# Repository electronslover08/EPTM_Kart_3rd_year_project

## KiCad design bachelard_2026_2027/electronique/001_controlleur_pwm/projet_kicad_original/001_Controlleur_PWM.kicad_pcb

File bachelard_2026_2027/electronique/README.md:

# ⚡ Électronique

Ce dossier contient les **schémas électroniques et les fichiers KiCad** du kart (KiCad 10) :

- **PCB de commande à distance** : lecture du récepteur radio, commande de l'accélération, du frein et de la direction, sélection du mode (manuel / à distance) ;
- **sécurités** : détection de la perte de liaison, arrêt d'urgence, chien de garde indépendant du microcontrôleur ;
- monitoring au volant et câblage.

Licence : [CERN-OHL-P-2.0](../../.github/LICENSES/CERN-OHL-P-2.0.txt). En cas de modification, indique la **date** et une **brève description** du changement (exigence de la licence).

## Contenu (état au 27.11.2026)

| Dossier | Contenu |
|---|---|
| [`001_controlleur_pwm/`](001_controlleur_pwm/) | Contrôleur PWM : lecture des 6 voies du récepteur, sortie RS-485. `projet_kicad_original/` = fichiers d'origine (ne pas modifier) ; `projet_kicad_version_eptm/` = version de travail pour la gravure EPTM (règles `.kicad_dru`, points de test dans `points_de_test.md`) |
| [`002_controleur_moteur/`](002_controleur_moteur/) | Contrôleur moteur : projet KICAD commencé (schéma, PCB vide) |
| [`xxx_modele_pcb/`](xxx_modele_pcb/) | Projet KiCad modèle, à copier pour un nouveau PCB |
| [`prompt_reprise_points_de_test_271126.md`](prompt_reprise_points_de_test_271126.md) | Note de reprise du PCB 001 : état, règles EPTM, points de test TP1 à TP7 |

## Bibliothèques tierces

Le symbole `lib_PIC18F45K22/PIC18F45K22-I_PT.kicad_sym` et l'empreinte TQFP-44 viennent de **SnapEDA / SnapMagic** (pièce Microchip PIC18F45K22-I/PT, récupérés le 26.11.2026). Ils ne sont **pas** sous les licences du reste du dépôt : SnapEDA les publie sous **CC BY-SA 4.0** avec l'exception « Design Exception 1.0 » (conditions complètes sur le site de SnapEDA). Source : <https://www.snapeda.com/parts/PIC18F45K22-I/PT/Microchip+Technology/view-part/>. Garde cette mention si tu modifies ces fichiers.

Le modèle 3D `lib_PIC18F45K22/3dmodels/PIC18F45K22-I_PT.step` est un modèle TQFP-44 **générique** retraité sous Open CASCADE (le modèle SnapEDA d'origine portait le nom `ATMEGA32-16AU`) : il ne représente que l'encombrement du boîtier. Les empreintes MAX485EESA (`lib_MAX485EESA`) sont des fichiers de bibliothèque de constructeur : leur origine exacte est à confirmer.

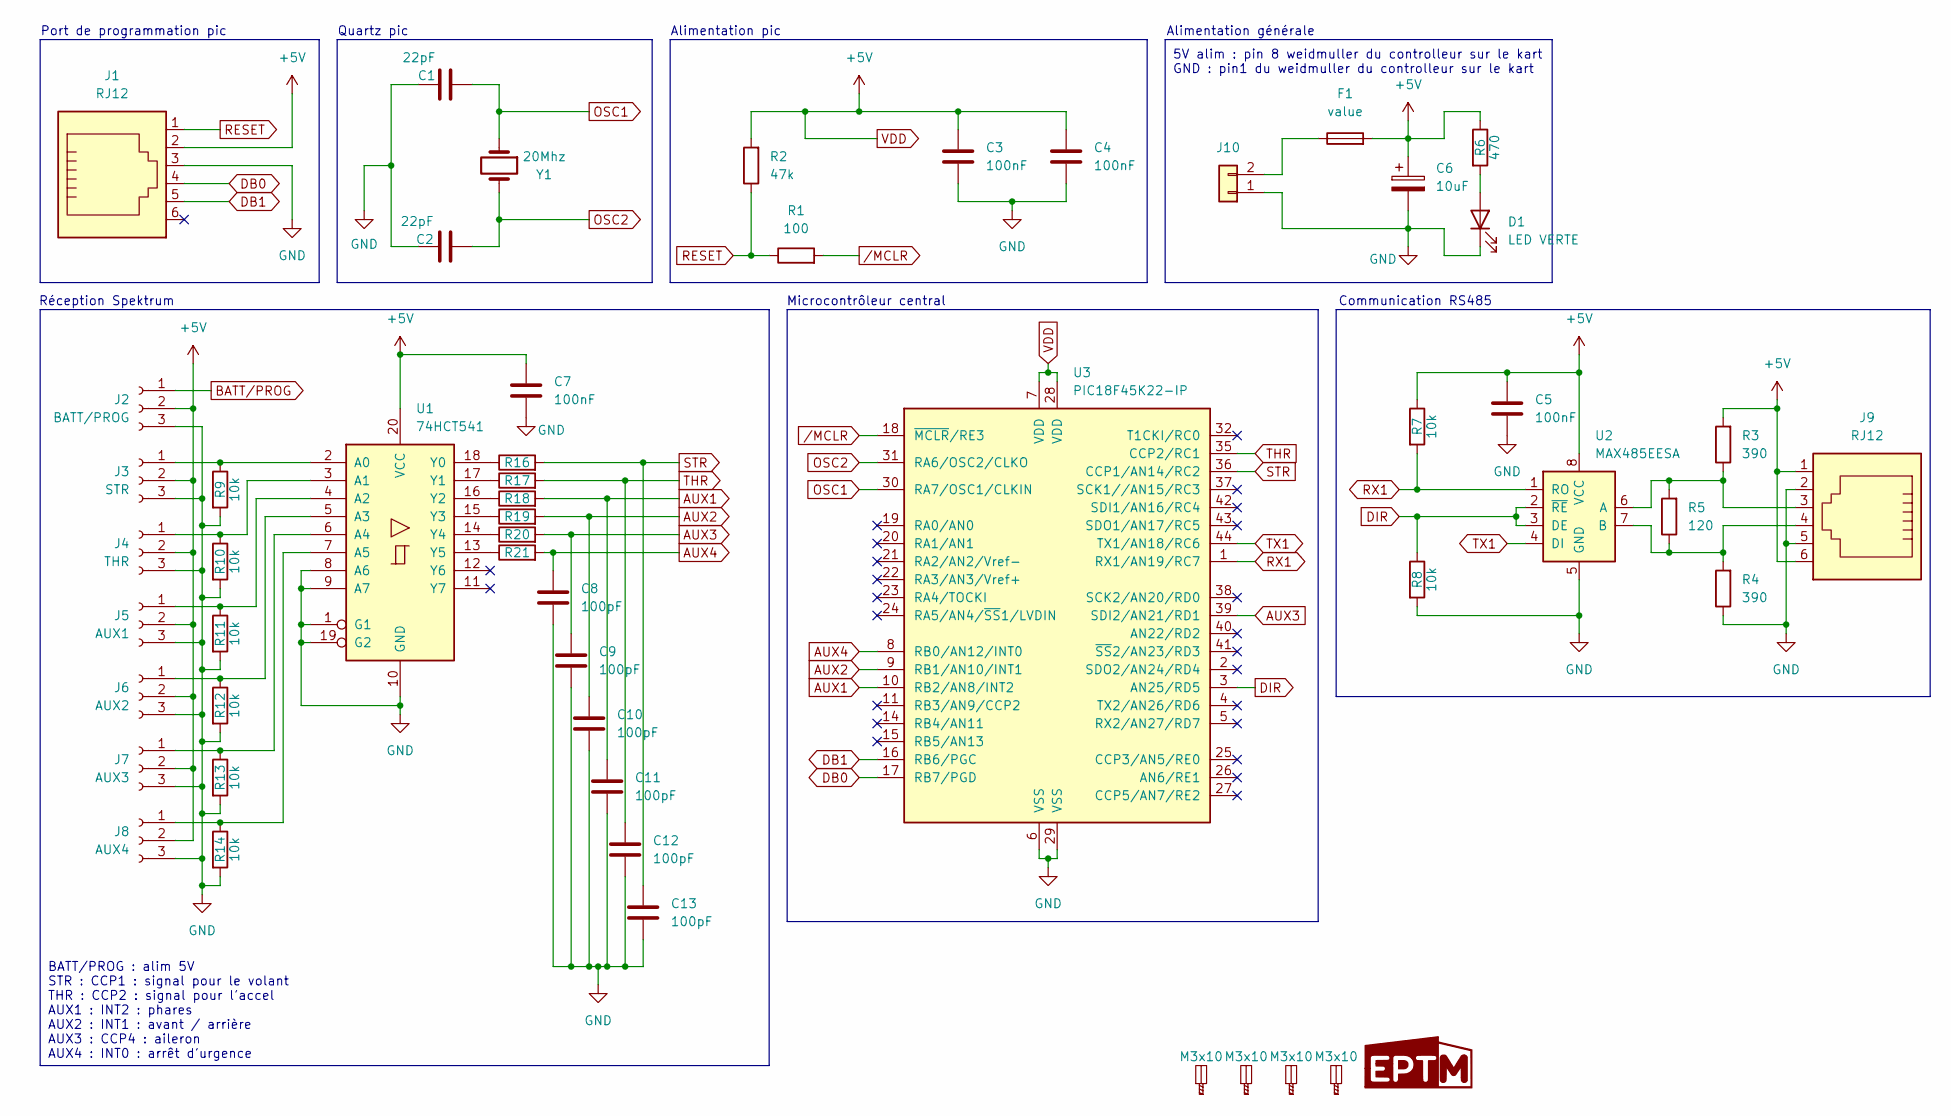
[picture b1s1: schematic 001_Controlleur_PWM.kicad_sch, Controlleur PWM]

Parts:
C1, C2: 22pF; C_0805_2012Metric_Pad1.18x1.45mm_HandSolder
C3, C4, C5, C7: 100nF; C_0805_2012Metric_Pad1.18x1.45mm_HandSolder
C6: 10uF; CP_Elec_6.3x7.7
C8, C9, C10, C11, C12, C13: 100pF; C_0805_2012Metric_Pad1.18x1.45mm_HandSolder
D1: LED VERTE; LED_SMD_1206_3216Metric_Pad1.42x1.75mm_HandSolder
F1: value; Fuseholder_Clip-5x20mm_P15.00x5.00mm_D1.3mm_Horizontal
J1, J9: RJ12; RJ12_Amphenol_54601-x06_Horizontal
J2: BATT/PROG; PinSocket_1x03_P2.54mm_Vertical
J3: STR; PinSocket_1x03_P2.54mm_Vertical
J4: THR; PinSocket_1x03_P2.54mm_Vertical
J5: AUX1; PinSocket_1x03_P2.54mm_Vertical
J6: AUX2; PinSocket_1x03_P2.54mm_Vertical
J7: AUX3; PinSocket_1x03_P2.54mm_Vertical
J8: AUX4; PinSocket_1x03_P2.54mm_Vertical
J10: SCREW_1x02_P5.08mm_Horizontal
M3x1, M3x2, M3x3, M3x4: M3x10; Spacer_M3x10mm
R1: 100; R_0805_2012Metric_Pad1.20x1.40mm_HandSolder
R2: 47k; R_0805_2012Metric_Pad1.20x1.40mm_HandSolder
R3, R4: 390; R_0805_2012Metric_Pad1.20x1.40mm_HandSolder
R5: 120; R_0805_2012Metric_Pad1.20x1.40mm_HandSolder
R6: 470; R_0805_2012Metric_Pad1.20x1.40mm_HandSolder
R7, R8, R9, R10, R11, R12, R13, R14: 10k; R_0805_2012Metric_Pad1.20x1.40mm_HandSolder
R16, R17, R18, R19, R20, R21: 1k; R_0805_2012Metric_Pad1.20x1.40mm_HandSolder
U1: 74HCT541; SOIC-20W_7.5x12.8mm_P1.27mm
U2: MAX485EESA; 21-0041B_8_MXM; MPN MAX485EESA
U3: PIC18F45K22-IP; TQFP-44_10x10mm_P0.8mm
U4: LOGO_EPTM_15mm_sérigraphie
Y1: 20Mhz; Crystal_SMD_HC49-SD_HandSoldering

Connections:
AUX1: C11.1, R18.2, U3.10 (RB2/AN8/INT2)
AUX2: C10.1, R19.2, U3.9 (RB1/AN10/INT1)
AUX3: C9.1, R20.2, U3.39 (SDI2/AN21/RD1)
AUX4: C8.1, R21.2, U3.8 (RB0/AN12/INT0)
BATT/PROG: J2.1
DB0: J1.4, U3.17 (RB7/PGD)
DB1: J1.5, U3.16 (RB6/PGC)
DIR: R8.1, U2.2 (~RE), U2.3 (DE), U3.3 (AN25/RD5)
GND: C1.2, C2.2, C3.2, C4.2, C5.2, C6.2, C7.2, C8.2, C9.2, C10.2, C11.2, C12.2, C13.2, D1.1 (K), J1.3, J2.3, J3.3, J4.3, J5.3, J6.3, J7.3, J8.3, J9.2, J9.5, J10.1, R4.1, R8.2, R9.2, R10.2, R11.2, R12.2, R13.2, R14.2, U1.1 (G1), U1.8 (A6), U1.9 (A7), U1.10 (GND), U1.19 (G2), U2.5 (GND), U3.6 (VSS), U3.29 (VSS)
unnamed: D1.2 (A), R6.2
unnamed: J3.1, R9.1, U1.2 (A0)
unnamed: J4.1, R10.1, U1.3 (A1)
unnamed: J5.1, R11.1, U1.4 (A2)
unnamed: J6.1, R12.1, U1.5 (A3)
unnamed: J7.1, R13.1, U1.6 (A4)
unnamed: J8.1, R14.1, U1.7 (A5)
unnamed: F1.1, J10.2
unnamed: R16.1, U1.18 (Y0)
unnamed: R17.1, U1.17 (Y1)
unnamed: R18.1, U1.16 (Y2)
unnamed: R19.1, U1.15 (Y3)
unnamed: R20.1, U1.14 (Y4)
unnamed: R21.1, U1.13 (Y5)
unnamed: J9.3, R3.1, R5.2, U2.6 (A)
unnamed: J9.4, R4.2, R5.1, U2.7 (B)
OSC1: C1.1, U3.30 (RA7/OSC1/CLKIN), Y1.1
OSC2: C2.1, U3.31 (RA6/OSC2/CLKO), Y1.2
RESET: J1.1, R1.1, R2.1
RX1: R7.2, U2.1 (RO), U3.1 (RX1/AN19/RC7)
STR: C13.1, R16.2, U3.36 (CCP1/AN14/RC2)
THR: C12.1, R17.2, U3.35 (CCP2/RC1)
TX1: U2.4 (DI), U3.44 (TX1/AN18/RC6)
VDD: C3.1, C4.1, C5.1, C6.1, C7.1, F1.2, J1.2, J2.2, J3.2, J4.2, J5.2, J6.2, J7.2, J8.2, J9.1, J9.6, R2.2, R3.2, R6.1, R7.1, U1.20 (VCC), U2.8 (VCC), U3.7 (VDD), U3.28 (VDD)
/MCLR: R1.2, U3.18 (~MCLR/RE3)

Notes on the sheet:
Alimentation générale
Microcontrôleur central
Quartz pic
Communication RS485
BATT/PROG : alim 5V STR : CCP1 : signal pour le volant THR : CCP2 : signal pour l'accel AUX1 : INT2 : phares AUX2 : INT1 : avant / arrière AUX3 : CCP4 : aileron AUX4 : INT0 : arrêt d'urgence
Port de programmation pic
5V alim : pin 8 weidmuller du controlleur sur le kart GND : pin1 du weidmuller du controlleur sur le kart
Réception Spektrum
Alimentation pic

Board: 2 copper layers, 54 parts (0 on the bottom side), 33 nets, no tracks yet.
